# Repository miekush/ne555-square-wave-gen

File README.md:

# NE555_Square_Wave_Generator
A Simple NE555 based Square Wave Generator with Adjustable Frequency

# License

MKE supports the open source hardware community by sharing hardware design files freely on GitHub!

Please support MKE by purchasing products on [Tindie](https://www.tindie.com/stores/mkengineering/)!

Designed by Mike Kushnerik for MKEngineering

Licensed under [Creative Commons Attribution-ShareAlike CC BY-SA 3.0](http://creativecommons.org/licenses/by-sa/3.0/)

All text above must be included in any redistribution!

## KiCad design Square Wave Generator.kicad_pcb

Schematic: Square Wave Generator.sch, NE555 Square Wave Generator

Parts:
C1, C3, C4: 0.1uF; C_Disc_D4.3mm_W1.9mm_P5.00mm
C2: 10uF; C_Disc_D4.3mm_W1.9mm_P5.00mm
D1: 5819; D_DO-41_SOD81_P7.62mm_Horizontal
H1, H2, H3, H4: MH; MountingHole_3.2mm_M3
J1: SIG; CT3149
J2: GND; CT3149
RV1: 10K; RM-065
SW1: POWER; OS102011MA1QN1_RA
TP1: BATT+; WIRE_SR_C
TP2: BATT-; WIRE_SR_R
U1: NE555; DIP-8_W7.62mm

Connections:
unnamed: C1.1, C2.1, SW1.2 (B), U1.4, U1.8
unnamed: C1.2, C2.2, C3.2, C4.2, J2.1, TP2.1, U1.1
unnamed: C3.1, U1.5
unnamed: C4.1, RV1.2, U1.2, U1.6
unnamed: D1.1 (K), SW1.1 (A)
unnamed: D1.2 (A), TP1.1
unnamed: J1.1, RV1.1, U1.3

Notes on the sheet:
Square Wave Generator - NE555 in Astable Configuration
Mounting

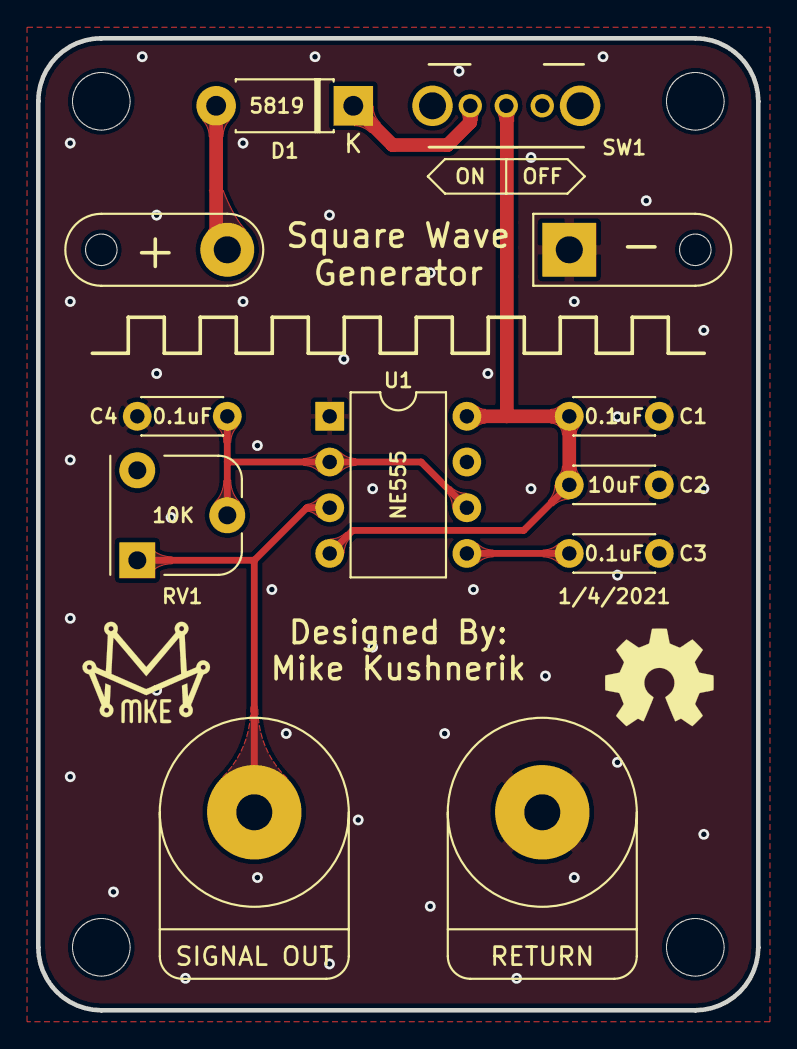
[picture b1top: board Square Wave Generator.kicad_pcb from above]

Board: 2 copper layers, 40.0 x 54.0 mm, 16 parts (0 on the bottom side), 7 nets.

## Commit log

2021-01-08 Add KiCad Files
2021-01-08 Add Images and License
